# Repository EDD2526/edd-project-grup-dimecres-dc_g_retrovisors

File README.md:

View this project on [CADLAB.io](https://cadlab.io/project/30190). 

# Projecte Retrovisors

>**Autors:Carlos Soler Fernandez, Ingrid López Sánchez ** 
>**Versió: final (v.3)**

----------

## Objectiu

>Poder obrir y tancar els retrovisors del cotxe
>Crear els leds de canvi de dirección i angle mort 
>Crear un defoger
>Poder ajustar els retrovisors del cotxe
>Dissenyar i fabricar un sistema electrònic integral per al control de retrovisors
>Gestionar els tres motors amb els finals de carrera on calgui
>Incorporar un sistema que medeixi quan es produeix enlluernament
>Planificar el muntatge de la placa tenint en compte les regles i esoecificacions del fabricant 
>Incorporar un sistema de calefacció i sensors digitals d'angle mort
>Assegurant la viabilitat tècnica i econòmica des del prototip fins a la producció a gran escala

## Diagrama de blocs

### Descripció/funcionalitat de cada bloc

  *

-----------

## Requisits / Especificacions

  * Alimentació; 12V, regulada 5V
  * Microcontrolador PIC18xxxxxxxxx
  * ...

-----------

## Components

| Descripci&#243; | Ref | Package |Datasheet | Prove&#239;dor | Preu | Unitats |
| --- | --- | --- | --- | ---| --- | --- |
| Microcontrolador | PIC18F26Q83-I/SS | SOIC-28 |[Datasheet](https://www.mouser.es/datasheet/2/268/PIC18F27_47_57Q83_Preliminary_Data_Sheet_40002265B-2887591.pdf) | [Mouser](https://www.mouser.es/c/?q=PIC18F27Q83-I%2FSO)| 2,17&euro;| 1x |
| XTAL-Ressonador | CSTCR7M99G53-R0 | SMD |[Datasheet](https://www.mouser.es/datasheet/2/281/p16e-522700.pdf) | [Mouser](https://www.mouser.es/ProductDetail/Murata-Electronics/CSTCR7M99G53-R0?qs=Zd9RUO93%2Fo7cnwzsujIkpA%3D%3D)  | 0,27&euro; | 1x |

-----------

## Software

### Eines:

  * KiCad 9.0 o superior
  * 

### Configuraci&#243; :

  * 

### Funcionalitats:

  * 

-----------

## Historial de canvis

| Data | Autor     | Branch | Versi&#243; | Descripci&#243; |
| --- | --- | --- | --- | --- |
| 11/03/2026 | iingridlopez | Master | prova | Inici del projecte 
| 17/03/2026 | canals-ub | Master | Backlink added | Backlink to CADLAB.io has been added. 
| 17/03/2026 | Carlosolerfernandez | Master | Create project kicad | Inici del projecte en KiCad 
| 17/03/2026 | Carlosolerfernandez | Master | Inici kiCat | Primera versió de l'esquemàtic 
| 17/03/2026 | Carlosolerfernandez | Master | Inici proyecta kicat | Configuració de fitxers inicials 
| 17/03/2026 | Carlosolerfernandez | Master | Etapa de alimentació 1 | Disseny de la primera part d'alimentació 
| 17/03/2026 | Carlosolerfernandez | Master | Etapa de alimentacio completa | Finalització de l'etapa d'alimentació 
| 17/03/2026 | Carlosolerfernandez | Master | Alimentacio finalitzada e inici de micro | Transició al disseny del microcontrolador 
| 18/03/2026 | Carlosolerfernandez | Master | microcontrolador i driver | Afegit microcontrolador i perifèrics 
| 22/03/2026 | Carlosolerfernandez | Master | Correcio gnd, proposicio canvi de micro | Correcció de masses i revisió de components 
| 23/03/2026 | Carlosolerfernandez | Master | Reorganització proyecte, inici conexions CAN | Gestió del bus CAN 
| 23/03/2026 | Carlosolerfernandez | Master | Part Micro quasi completat | Falta afegir etiquetes de potencia 
| 24/03/2026 | Carlosolerfernandez | Master | Microprocessador finalissim | Placement de alimentacion y micro 
| 25/03/2026 | Carlosolerfernandez | Master | Diagrama de Blocs Afegit | Canvi del swicht1 to push botton5 
| 29/03/2026 | iingridlopez | Branca Nova | Creacio de branca nova i update | Inici de nova branca de treball 
| 07/04/2026 | iingridlopez | Master | actualització (NO VERSIÓ FINAL) | Sincronització de canvis |
| 08/04/2026 | iingridlopez | Master | esquematic + placement | Falta routing dels drivers 
| 08/04/2026 | Carlosolerfernandez | Master | README | Creació del fitxer de documentació 
| 08/04/2026 | iingridlopez | Master | añadido el readme | Actualització de documentació 
| 08/04/2026 | Carlosolerfernandez | Master | Modificació placement | Ajustos en la placa 
| 08/04/2026 | iingridlopez | Master | prueba para unir a la main | Test de merge 
| 08/04/2026 | iingridlopez | Master | Merge con resolución de conflictos | Unió de branques en KiCad 
| 08/04/2026 | Carlosolerfernandez | Master | afegim diagrama | Actualització gràfica del projecte 
| 08/04/2026 | Carlosolerfernandez | Master | Correccion Readme | Revisió de textos 
| 08/04/2026 | Carlosolerfernandez | Master | eliminamos GND PWR | Modificació de tots els GND 
| 10/04/2026 | iingridlopez | Master | millora de placement | Optimització d'espai 
| 13/04/2026 | Carlosolerfernandez | Master | Enrotament Part digital finalitzada | Finalització del routing digital |

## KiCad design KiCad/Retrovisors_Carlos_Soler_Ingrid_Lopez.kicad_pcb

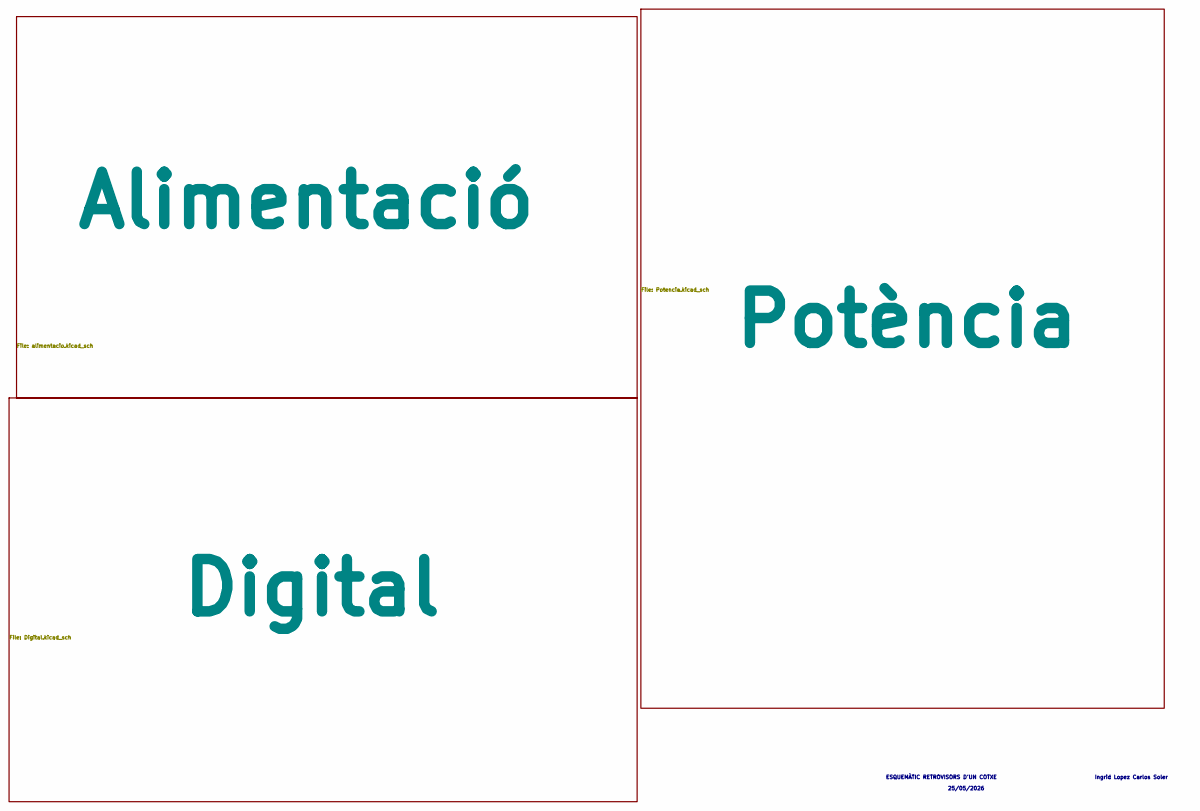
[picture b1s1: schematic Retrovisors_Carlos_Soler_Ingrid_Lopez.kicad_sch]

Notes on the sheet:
Ingrid Lopez Carlos Soler
ESQUEMÀTIC RETROVISORS D'UN COTXE
25/05/2026

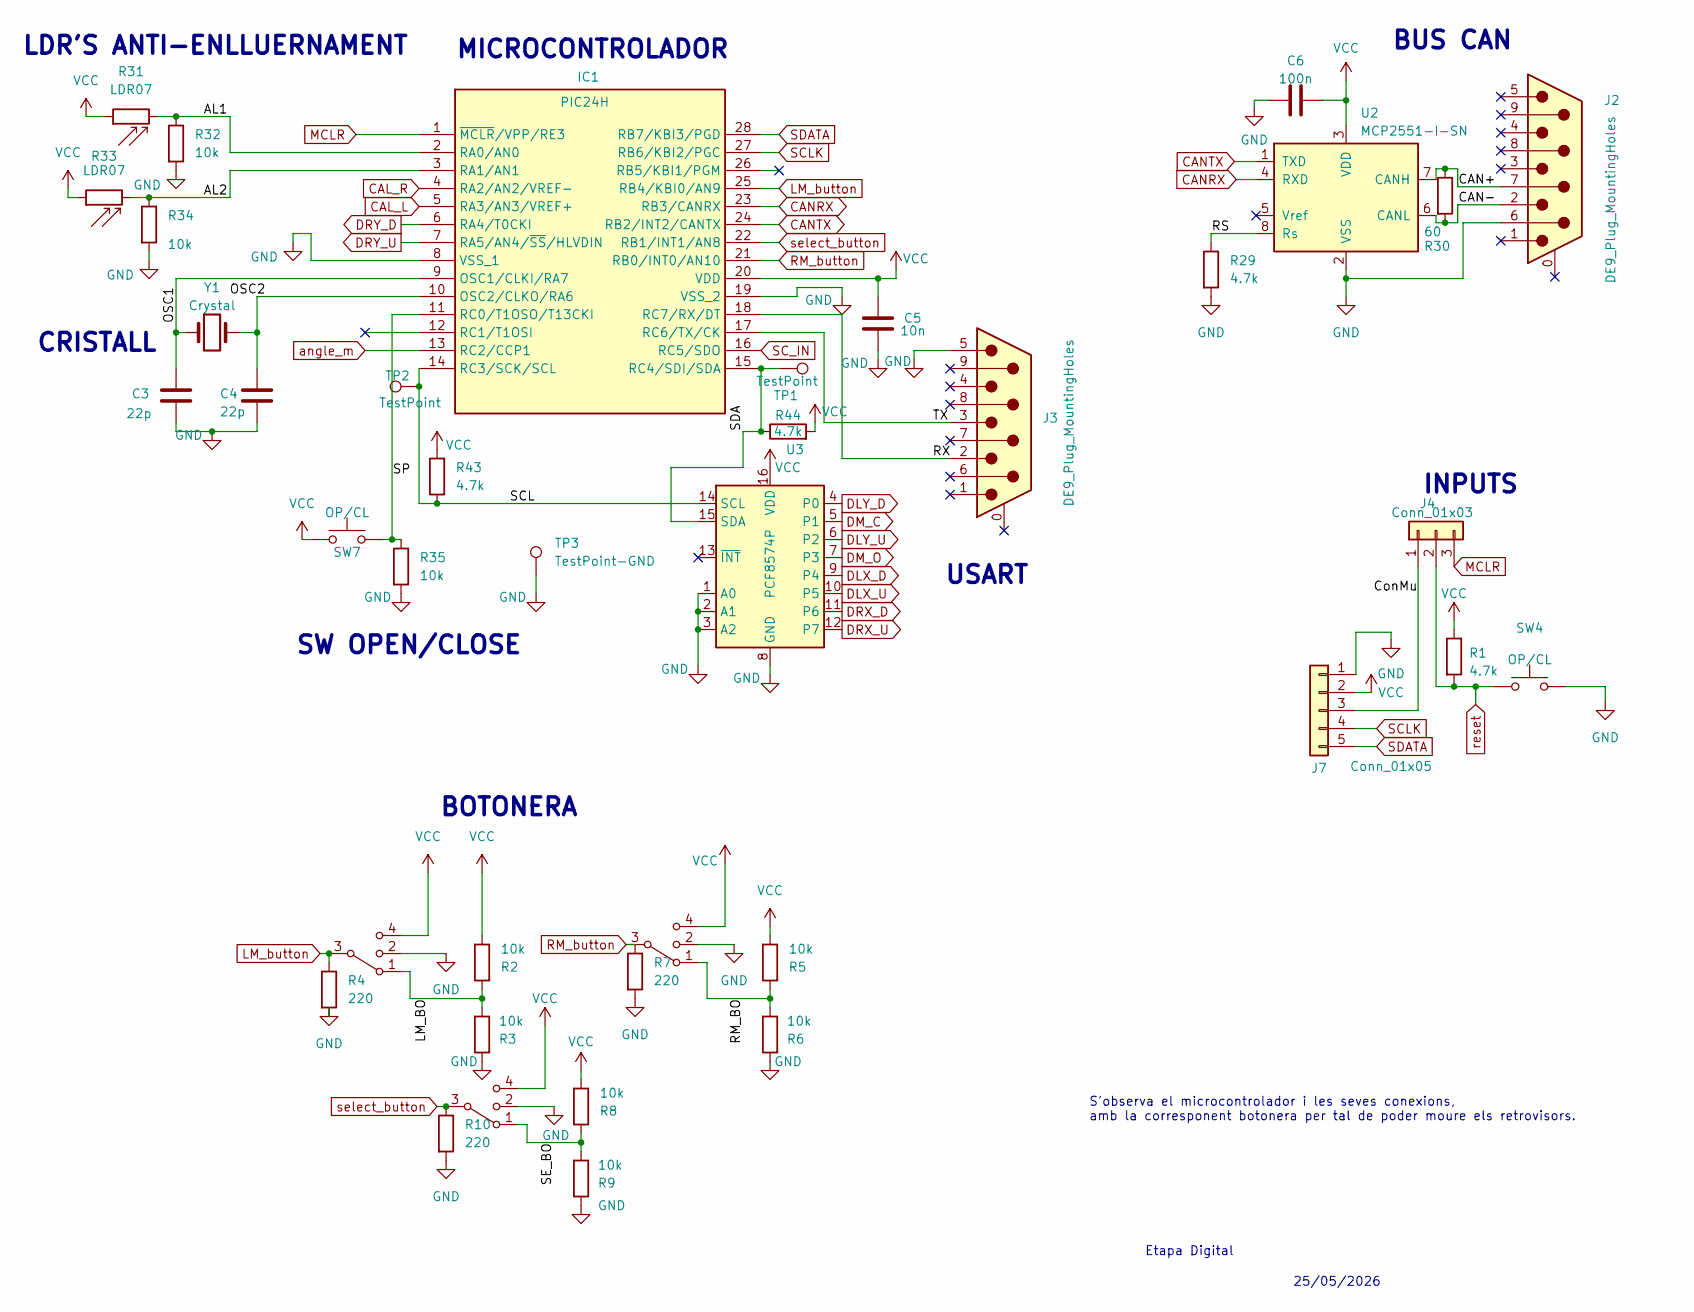
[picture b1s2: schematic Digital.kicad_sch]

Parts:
C3, C4: 22p; C_0805_2012Metric_Pad1.18x1.45mm_HandSolder
C5: 10n; C_0805_2012Metric_Pad1.18x1.45mm_HandSolder
C6: 100n; C_0805_2012Metric_Pad1.18x1.45mm_HandSolder
IC1: PIC24H; SOIC127P1030X265-28N; Manufacturer_Part_Number PIC18F2580-I/SO; Mouser Part Number 579-PIC18F2580-I/SO
J2, J3: DE9_Plug_MountingHoles; DSUB-9_Female_Vertical_Pitch2.77x2.84mm_MountingHoles
J4: Conn_01x03; PinHeader_1x03_P2.54mm_Vertical
J7: Conn_01x05; PinHeader_1x05_P2.54mm_Vertical
R1, R29, R43, R44: 4.7k; R_1206_3216Metric_Pad1.30x1.75mm_HandSolder
R2, R3, R5, R6, R8, R9, R32, R34, R35: 10k; R_1206_3216Metric_Pad1.30x1.75mm_HandSolder
R4, R7, R10: 220; R_1206_3216Metric_Pad1.30x1.75mm_HandSolder
R30: 60; R_1206_3216Metric_Pad1.30x1.75mm_HandSolder
R31, R33: LDR07; R_LDR_5.1x4.3mm_P3.4mm_Vertical
SW1, SW2, SW3: SW_DP3T; SW_DIP_SPSTx02_Piano_10.8x6.64mm_W7.62mm_P2.54mm
SW4, SW7: OP/CL; SW_SPST_PTS647_Sx38
TP1, TP2: TestPoint; TestPoint_THTPad_D1.5mm_Drill0.7mm
TP3: TestPoint-GND; TestPoint_THTPad_D1.5mm_Drill0.7mm
U2: MCP2551-I-SN; SOIC-8_3.9x4.9mm_P1.27mm
U3: PCF8574P; DIP-16_W7.62mm
Y1: Crystal; Crystal_SMD_Abracon_ABM3-2Pin_5.0x3.2mm_HandSoldering

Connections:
/Digital/AL1: IC1.2 (RA0/AN0), R31.2, R32.1
/Digital/AL2: IC1.3 (RA1/AN1), R33.2, R34.1
/Digital/CAN+: J2.7, R30.1, U2.7 (CANH)
/Digital/CAN-: J2.2, R30.2, U2.6 (CANL)
/Digital/ConMu: J4.1, J7.3
/Digital/LM_BO: R2.1, R3.2, SW2.1
/Digital/OSC1: C3.1, IC1.9 (OSC1/CLKI/RA7), Y1.1
/Digital/OSC2: C4.1, IC1.10 (OSC2/CLKO/RA6), Y1.2
/Digital/RM_BO: R5.1, R6.2, SW1.1
/Digital/RS: R29.1, U2.8 (Rs)
/Digital/RX: IC1.18 (RC7/RX/DT), J3.2
/Digital/SCL: IC1.14 (RC3/SCK/SCL), R43.1, TP2.1, U3.14 (SCL)
/Digital/SDA: IC1.15 (RC4/SDI/SDA), R44.1, TP1.1, U3.15 (SDA)
/Digital/SE_BO: R8.1, R9.2, SW3.1
/Digital/SP: IC1.11 (RC0/T1OSO/T13CKI), R35.1, SW7.2
/Digital/TX: IC1.17 (RC6/TX/CK), J3.3
CAL_L: IC1.5 (RA3/AN3/VREF+); also elsewhere on the board
CAL_R: IC1.4 (RA2/AN2/VREF-); also elsewhere on the board
CANRX: IC1.23 (RB3/CANRX), U2.4 (RXD)
CANTX: IC1.24 (RB2/INT2/CANTX), U2.1 (TXD)
DLX_D: U3.9 (P4); also elsewhere on the board
DLX_U: U3.10 (P5); also elsewhere on the board
DLY_D: U3.4 (P0); also elsewhere on the board
DLY_U: U3.6 (P2); also elsewhere on the board
DM_C: U3.5 (P1); also elsewhere on the board
DM_O: U3.7 (P3); also elsewhere on the board
DRX_D: U3.11 (P6); also elsewhere on the board
DRX_U: U3.12 (P7); also elsewhere on the board
DRY_D: IC1.6 (RA4/T0CKI); also elsewhere on the board
DRY_U: IC1.7 (RA5/AN4/~SS/HLVDIN); also elsewhere on the board
GND: C3.2, C4.2, C5.2, C6.1, IC1.8 (VSS_1), IC1.19 (VSS_2), J2.6, J3.5, J7.1, R3.1, R4.2, R6.1, R7.2, R9.1, R10.2, R29.2, R32.2, R34.2, R35.2, SW1.2, SW2.2, SW3.2, SW4.2, TP3.1, U2.2 (VSS), U3.1 (A0), U3.2 (A1), U3.3 (A2), U3.8 (GND); also elsewhere on the board
LM_button: IC1.25 (RB4/KBI0/AN9), R4.1, SW2.3
MCLR: IC1.1 (~MCLR/VPP/RE3), J4.3
RM_button: IC1.21 (RB0/INT0/AN10), R7.1, SW1.3
SCLK: IC1.27 (RB6/KBI2/PGC), J7.4
SC_IN: IC1.16 (RC5/SDO); also elsewhere on the board
SDATA: IC1.28 (RB7/KBI3/PGD), J7.5
VCC: C5.1, C6.2, IC1.20 (VDD), J7.2, R1.1, R2.2, R5.2, R8.2, R31.1, R33.1, R43.2, R44.2, SW1.4, SW2.4, SW3.4, SW7.1, U2.3 (VDD), U3.16 (VDD); also elsewhere on the board
angle_m: IC1.13 (RC2/CCP1); also elsewhere on the board
reset: J4.2, R1.2, SW4.1
select_button: IC1.22 (RB1/INT1/AN8), R10.1, SW3.3

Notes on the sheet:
LDR'S ANTI-ENLLUERNAMENT
25/05/2026
BUS CAN
SW OPEN/CLOSE
USART
S'observa el microcontrolador i les seves conexions, amb la corresponent botonera per tal de poder moure els retrovisors.
MICROCONTROLADOR
BOTONERA
INPUTS
CRISTALL
Etapa Digital

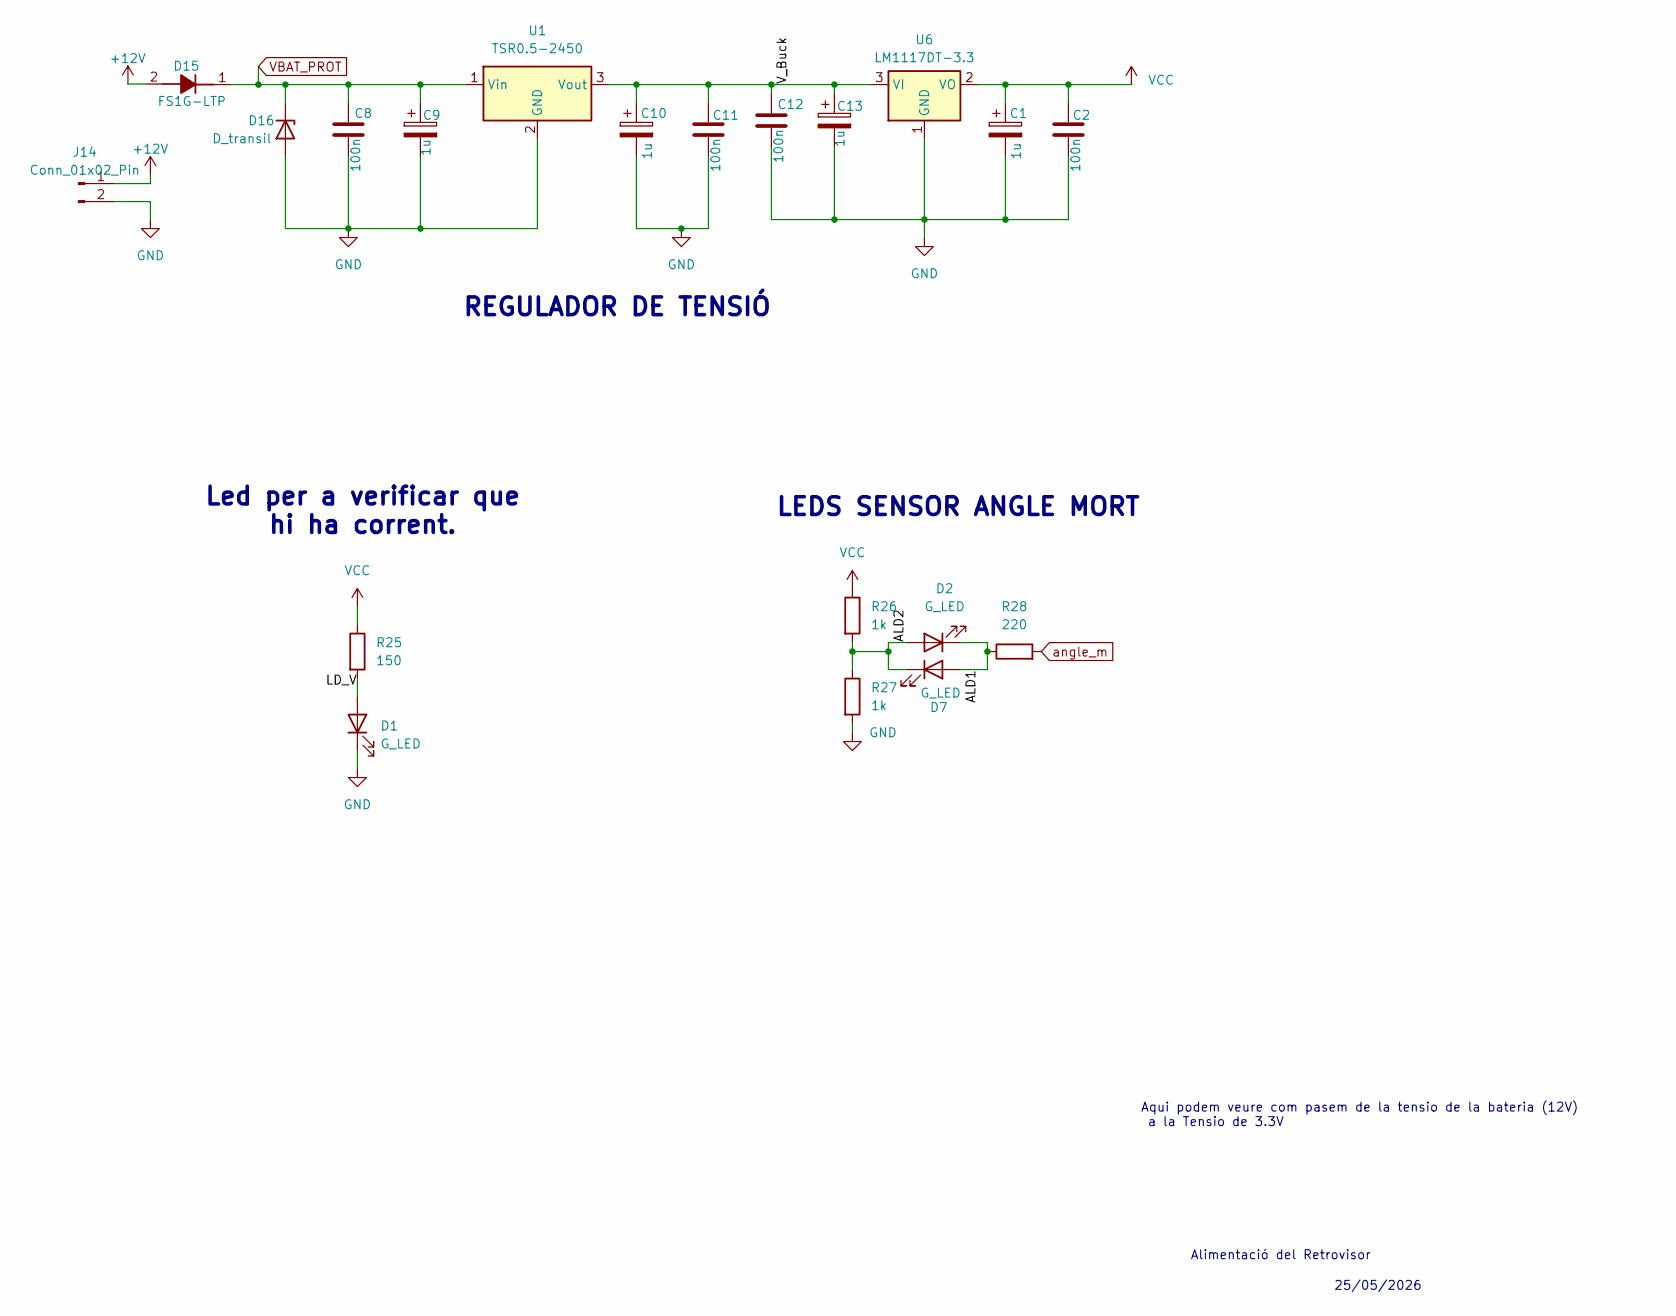
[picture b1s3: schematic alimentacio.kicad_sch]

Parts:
C1, C9, C10, C13: 1u; CP_Elec_4x5.7
C2, C8, C11, C12: 100n; C_0805_2012Metric_Pad1.18x1.45mm_HandSolder
D1, D2, D7: G_LED; LED_0805_2012Metric_Pad1.15x1.40mm_HandSolder
D15: FS1G-LTP; DIOM5225X244N; Manufacturer_Part_Number FS1G-LTP; Mouser Part Number 833-FS1G-LTP
D16: D_transil; D_DO-35_SOD27_P2.54mm_Vertical_AnodeUp
J14: Conn_01x02_Pin; PinHeader_1x02_P2.54mm_Vertical
R25: 150; R_0805_2012Metric_Pad1.20x1.40mm_HandSolder
R26, R27: 1k; R_1206_3216Metric_Pad1.30x1.75mm_HandSolder
R28: 220; R_1206_3216Metric_Pad1.30x1.75mm_HandSolder
U1: TSR0.5-2450; Converter_DCDC_TRACO_TSR0.5-24xx_TSR0.5-24xxx_THT
U6: LM1117DT-3.3; TO-252-3_TabPin2

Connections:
+12V: D15.2 (A), J14.1
/Alimentació/ALD1: D2.1 (K), D7.2 (A), R28.1
/Alimentació/ALD2: D2.2 (A), D7.1 (K), R26.2, R27.1
/Alimentació/LD_V: D1.2 (A), R25.2
/Alimentació/V_Buck: C10.1, C11.1, C12.1, C13.1, U1.3 (Vout), U6.3 (VI)
GND: C1.2, C2.2, C8.2, C9.2, C10.2, C11.2, C12.2, C13.2, D1.1 (K), D16.2 (A), J14.2, R27.2, U1.2 (GND), U6.1 (GND); also elsewhere on the board
VBAT_PROT: C8.1, C9.1, D15.1 (K), D16.1 (K), U1.1 (Vin); also elsewhere on the board
VCC: C1.1, C2.1, R25.1, R26.1, U6.2 (VO); also elsewhere on the board
angle_m: R28.2; also elsewhere on the board

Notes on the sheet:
REGULADOR DE TENSIÓ
25/05/2026
Led per a verificar que hi ha corrent.
LEDS SENSOR ANGLE MORT
Aqui podem veure com pasem de la tensio de la bateria (12V) a la Tensio de 3.3V
Alimentació del Retrovisor

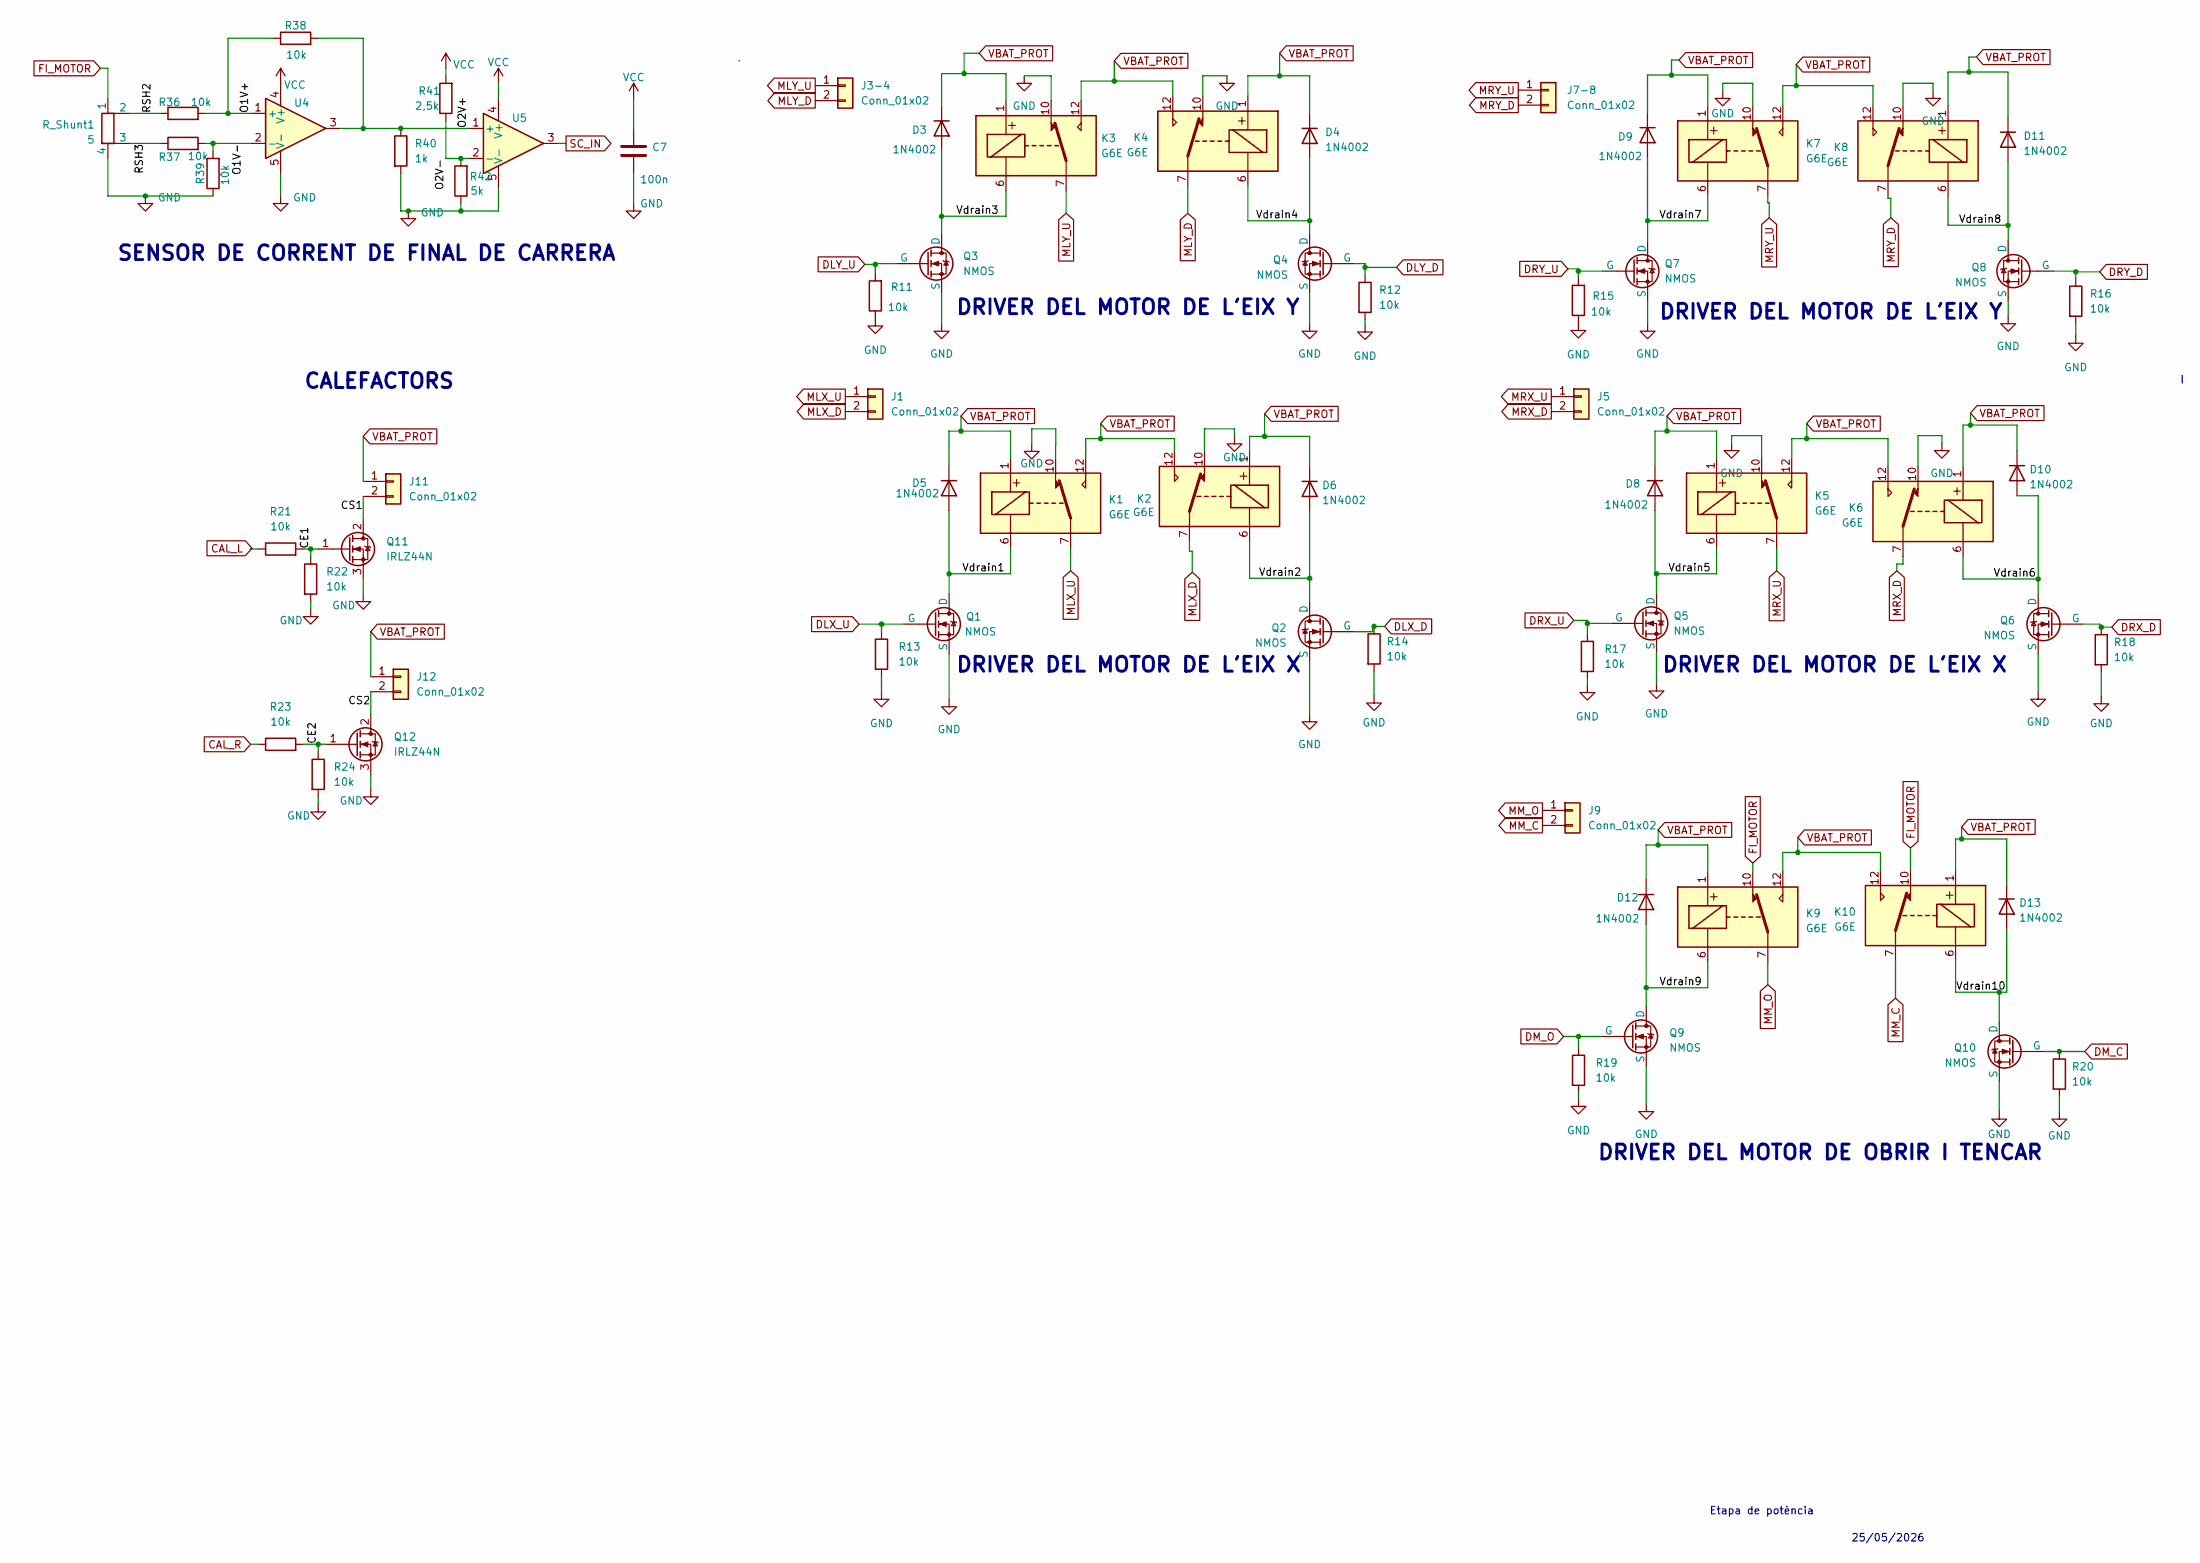
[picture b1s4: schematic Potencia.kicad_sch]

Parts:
C7: 100n; C_0805_2012Metric_Pad1.18x1.45mm_HandSolder
D3, D4, D5, D6, D8, D9, D10, D11, D12, D13: 1N4002; D_DO-41_SOD81_P10.16mm_Horizontal
J1, J3-4, J5, J7-8, J9, J11, J12: Conn_01x02; PinHeader_1x02_P2.54mm_Vertical
K1, K2, K3, K4, K5, K6, K7, K8, K9, K10: G6E; Relay_SPDT_Omron_G6E
Q1, Q2, Q3, Q4, Q5, Q6, Q7, Q8, Q9, Q10: NMOS; TO254P470X1016X1965-3P
Q11, Q12: IRLZ44N; TO-220-3_Vertical
R11, R12, R13, R14, R15, R16, R17, R18, R19, R20, R21, R22, R23, R24, R36, R37, R38, R39: 10k; R_1206_3216Metric_Pad1.30x1.75mm_HandSolder
R40: 1k; R_1206_3216Metric_Pad1.30x1.75mm_HandSolder
R41: 2,5k; R_1206_3216Metric_Pad1.30x1.75mm_HandSolder
R42: 5k; R_1206_3216Metric_Pad1.30x1.75mm_HandSolder
R_Shunt1: 5; R_Shunt_Ohmite_LVK12
U4, U5: type="X" model="OPAMP" lib=""; SOT95P280X145-5N

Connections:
/Potencia/CE1: Q11.1 (G), R21.2, R22.1
/Potencia/CE2: Q12.1 (G), R23.2, R24.1
/Potencia/CS1: J11.2, Q11.2 (D)
/Potencia/CS2: J12.2, Q12.2 (D)
/Potencia/O1V+: R36.2, R38.1, U4.1 (+)
/Potencia/O1V-: R37.2, R39.2, U4.2 (-)
/Potencia/O2V+: R38.2, R40.1, U4.3, U5.1 (+)
/Potencia/O2V-: R41.1, R42.2, U5.2 (-)
/Potencia/RSH2: R36.1, R_Shunt1.2
/Potencia/RSH3: R37.1, R_Shunt1.3
/Potencia/Vdrain1: D5.2 (A), K1.6, Q1.1 (D)
/Potencia/Vdrain2: D6.2 (A), K2.6, Q2.1 (D)
/Potencia/Vdrain3: D3.2 (A), K3.6, Q3.1 (D)
/Potencia/Vdrain4: D4.2 (A), K4.6, Q4.1 (D)
/Potencia/Vdrain5: D8.2 (A), K5.6, Q5.1 (D)
/Potencia/Vdrain6: D10.2 (A), K6.6, Q6.1 (D)
/Potencia/Vdrain7: D9.2 (A), K7.6, Q7.1 (D)
/Potencia/Vdrain8: D11.2 (A), K8.6, Q8.1 (D)
/Potencia/Vdrain9: D12.2 (A), K9.6, Q9.1 (D)
/Potencia/Vdrain10: D13.2 (A), K10.6, Q10.1 (D)
CAL_L: R21.1; also elsewhere on the board
CAL_R: R23.1; also elsewhere on the board
DLX_D: Q2.2 (G), R14.1; also elsewhere on the board
DLX_U: Q1.2 (G), R13.1; also elsewhere on the board
DLY_D: Q4.2 (G), R12.1; also elsewhere on the board
DLY_U: Q3.2 (G), R11.2; also elsewhere on the board
DM_C: Q10.2 (G), R20.1; also elsewhere on the board
DM_O: Q9.2 (G), R19.1; also elsewhere on the board
DRX_D: Q6.2 (G), R18.1; also elsewhere on the board
DRX_U: Q5.2 (G), R17.1; also elsewhere on the board
DRY_D: Q8.2 (G), R16.1; also elsewhere on the board
DRY_U: Q7.2 (G), R15.2; also elsewhere on the board
FI_MOTOR: K9.10, K10.10, R_Shunt1.1
GND: C7.2, K1.10, K2.10, K3.10, K4.10, K5.10, K6.10, K7.10, K8.10, Q1.3 (S), Q2.3 (S), Q3.3 (S), Q4.3 (S), Q5.3 (S), Q6.3 (S), Q7.3 (S), Q8.3 (S), Q9.3 (S), Q10.3 (S), Q11.3 (S), Q12.3 (S), R11.1, R12.2, R13.2, R14.2, R15.1, R16.2, R17.2, R18.2, R19.2, R20.2, R22.2, R24.2, R39.1, R40.2, R42.1, R_Shunt1.4, U4.5 (V-), U5.5 (V-); also elsewhere on the board
MLX_D: J1.2, K2.7
MLX_U: J1.1, K1.7
MLY_D: J3-4.2, K4.7
MLY_U: J3-4.1, K3.7
MM_C: J9.2, K10.7
MM_O: J9.1, K9.7
MRX_D: J5.2, K6.7
MRX_U: J5.1, K5.7
MRY_D: J7-8.2, K8.7
MRY_U: J7-8.1, K7.7
SC_IN: U5.3; also elsewhere on the board
VBAT_PROT: D3.1 (K), D4.1 (K), D5.1 (K), D6.1 (K), D8.1 (K), D9.1 (K), D10.1 (K), D11.1 (K), D12.1 (K), D13.1 (K), J11.1, J12.1, K1.1, K1.12, K2.1, K2.12, K3.1, K3.12, K4.1, K4.12, K5.1, K5.12, K6.1, K6.12, K7.1, K7.12, K8.1, K8.12, K9.1, K9.12, K10.1, K10.12; also elsewhere on the board
VCC: C7.1, R41.2, U4.4 (V+), U5.4 (V+); also elsewhere on the board

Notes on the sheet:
25/05/2026
DRIVER DEL MOTOR DE OBRIR I TENCAR
SENSOR DE CORRENT DE FINAL DE CARRERA
Etapa de potència
DRIVER DEL MOTOR DE L'EIX Y
DRIVER DEL MOTOR DE L'EIX X
CALEFACTORS

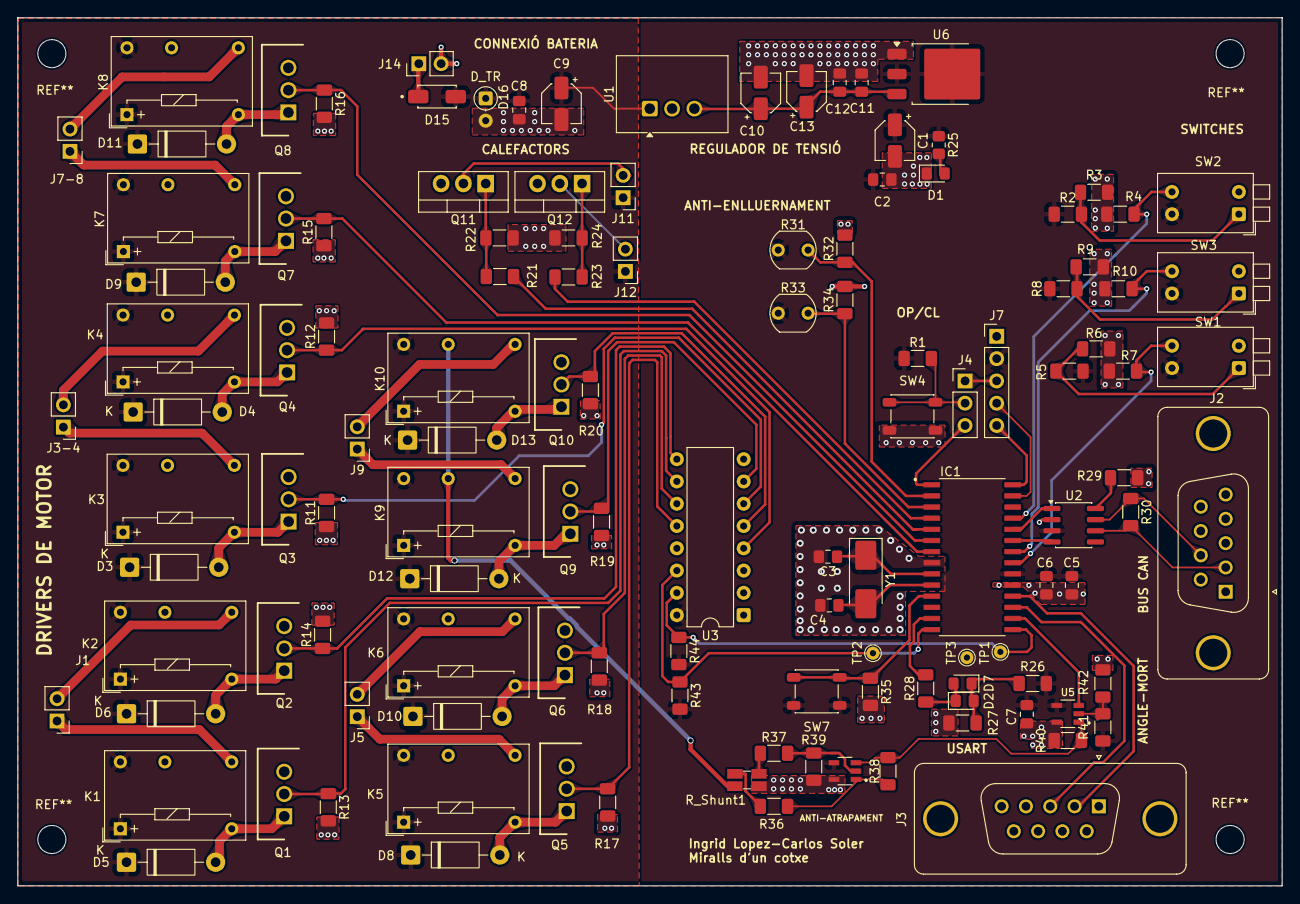
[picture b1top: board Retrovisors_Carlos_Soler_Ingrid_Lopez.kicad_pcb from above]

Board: 2 copper layers, 144.1 x 99.0 mm, 123 parts (0 on the bottom side), 78 nets.

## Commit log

2026-03-11 prova
2026-03-16 Backlink to CADLAB.io has been added.
2026-03-17 Create project kicad
2026-03-17 Inici kiCat
2026-03-17 Etapa de alimentació 1
2026-03-17 Etapa de alimentacio completa
2026-03-17 Alimentacio finalitzada e inici de micro
2026-03-18 microcontrolador i driver
2026-03-22 Correcio gnd, proposicio canvi de micro
2026-03-23 Reorganització proyecte, inici conexions CAN
2026-03-23 Part Micro quasi completat, falta afegir etiquetes de potencia
2026-03-24 Microprocessador finalissim + placement de alimentacion y micro
2026-03-25 Diagrama de Blocs Afegit, mes canvi del swicht1 to push botton5
2026-03-29 Creacio de branca nova i update
2026-04-07 actualització (NO VERSIÓ FINAL)
2026-04-08 esquematic + placement (FALTA ROUTING DELS DRIVERS!!)
2026-04-08 README
    PONIENDO README
2026-04-08 añadido el readme
2026-04-08 Modificació placement
2026-04-08 prueba para unir a la main
2026-04-08 afegim diagrama
2026-04-08 Correccion Readme
2026-04-08 modificando todos los GND eliminamos GND PWR
2026-04-10 millora de placement
2026-04-13 Enrotament Part digital finalitzada
2026-04-14 canvis en el readme, a més de petites modificacions de PCB part digital
2026-04-14 correccio error historial de canvis
2026-04-14 afegir expansor de i2C de 8 pins
2026-04-14 afegit esquematic (testpoints + extensor de pines) falta acabar placement
2026-04-14 canvis placement, afegir els r4emplazos que hi han a la pcb
2026-04-15 correcions de pcb
2026-04-18 placa abans de canvi placement 1
2026-04-18 pcb Tota connectada
2026-04-20 final de pcb, falta els test points
2026-04-21 petites modificacions resistencies part digital + resolucio errors pcb
2026-04-27 canvis pcb finals
2026-04-27 pcb definitiva
2026-04-28 placa definitivisima
2026-04-28 diseny final final
2026-04-28 definitiu
2026-04-29 afegit tot final
2026-04-29 Version final + readme
